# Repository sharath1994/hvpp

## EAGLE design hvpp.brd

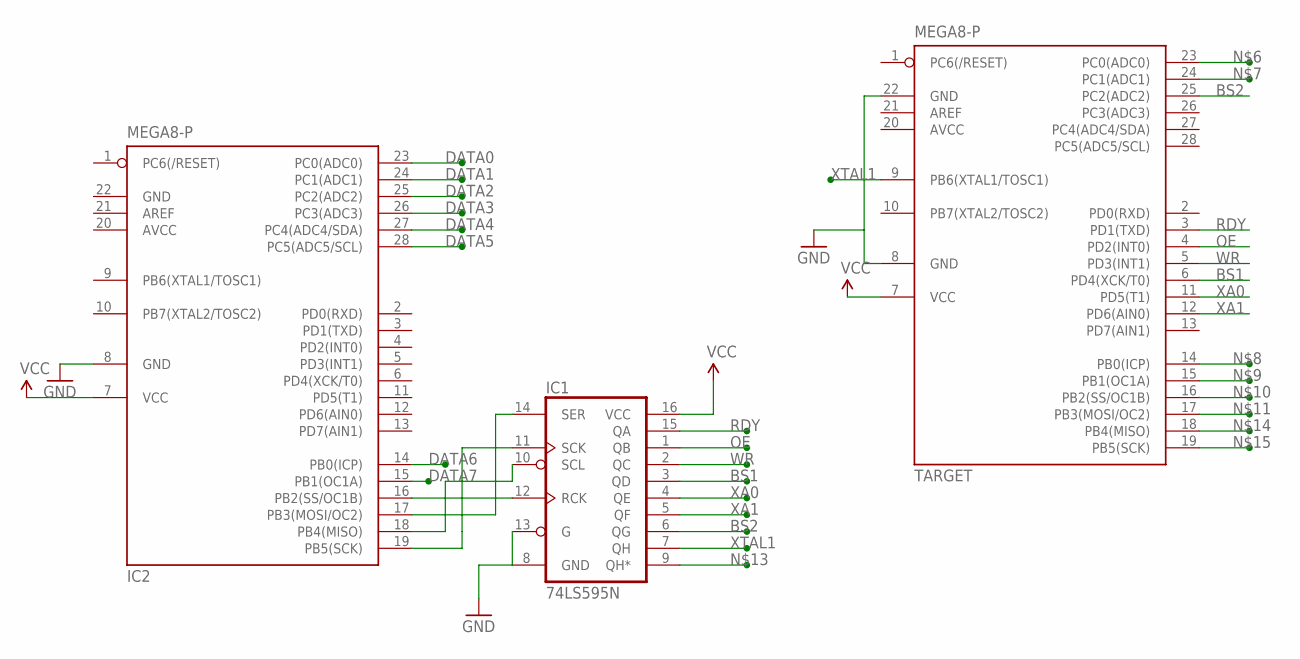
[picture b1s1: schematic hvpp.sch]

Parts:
IC1: 74LS595N; DIL16
IC2: MEGA8-P; DIL28-3
TARGET: MEGA8-P; DIL28-3

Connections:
AVCC: IC2.20 (AVCC), TARGET.20 (AVCC)
BS1: IC1.3 (QD), TARGET.6 (PD4(XCK/T0))
BS2: IC1.6 (QG), TARGET.25 (PC2(ADC2))
DATA0: IC2.23 (PC0(ADC0))
DATA1: IC2.24 (PC1(ADC1))
DATA2: IC2.25 (PC2(ADC2))
DATA3: IC2.26 (PC3(ADC3))
DATA4: IC2.27 (PC4(ADC4/SDA))
DATA5: IC2.28 (PC5(ADC5/SCL))
DATA6: IC2.14 (PB0(ICP))
DATA7: IC2.15 (PB1(OC1A))
GND: IC1.8 (GND), IC1.13 (G), IC2.8 (GND), IC2.22 (GND), TARGET.8 (GND), TARGET.22 (GND)
unnamed: IC1.11 (SCK), IC2.19 (PB5(SCK))
unnamed: IC1.14 (SER), IC2.17 (PB3(MOSI/OC2))
unnamed: IC1.12 (RCK), IC2.16 (PB2(SS/OC1B))
unnamed: IC1.10 (SCL), IC2.18 (PB4(MISO))
OE: IC1.1 (QB), TARGET.4 (PD2(INT0))
RDY: IC1.15 (QA), TARGET.3 (PD1(TXD))
VCC: IC1.16 (VCC), IC2.7 (VCC), TARGET.7 (VCC)
WR: IC1.2 (QC), TARGET.5 (PD3(INT1))
XA0: IC1.4 (QE), TARGET.11 (PD5(T1))
XA1: IC1.5 (QF), TARGET.12 (PD6(AIN0))
XTAL1: IC1.7 (QH), TARGET.9 (PB6(XTAL1/TOSC1))

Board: 2 copper layers, 3 parts (0 on the bottom side), 15 nets, no tracks yet.

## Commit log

2015-01-25 :tada: Added .gitattributes & .gitignore files
2015-01-25 first
2015-01-25 initial V-USB firmware skeleton
2015-01-25 test
2015-01-25 fix inital skeleton: don't rely on local USBaspLoader

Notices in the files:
parts and their libraries:
SparkFun: Licensing: CC v3.0 Share-Alike You are welcome to use this library for commercial purposes.
